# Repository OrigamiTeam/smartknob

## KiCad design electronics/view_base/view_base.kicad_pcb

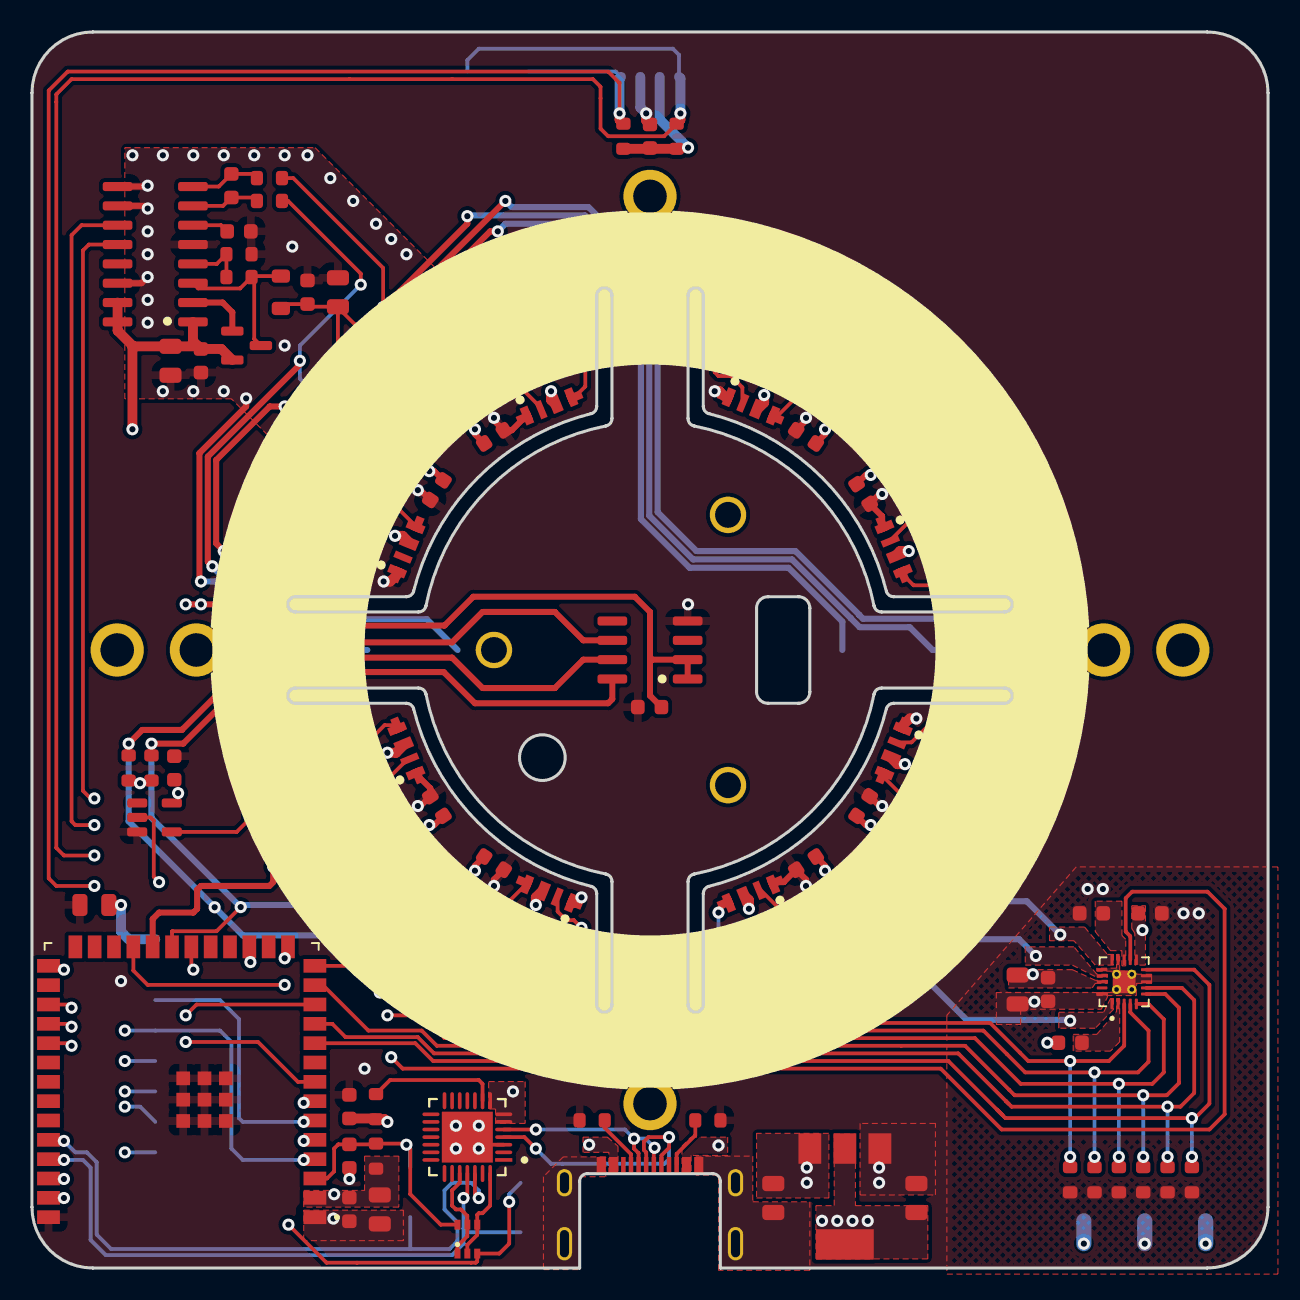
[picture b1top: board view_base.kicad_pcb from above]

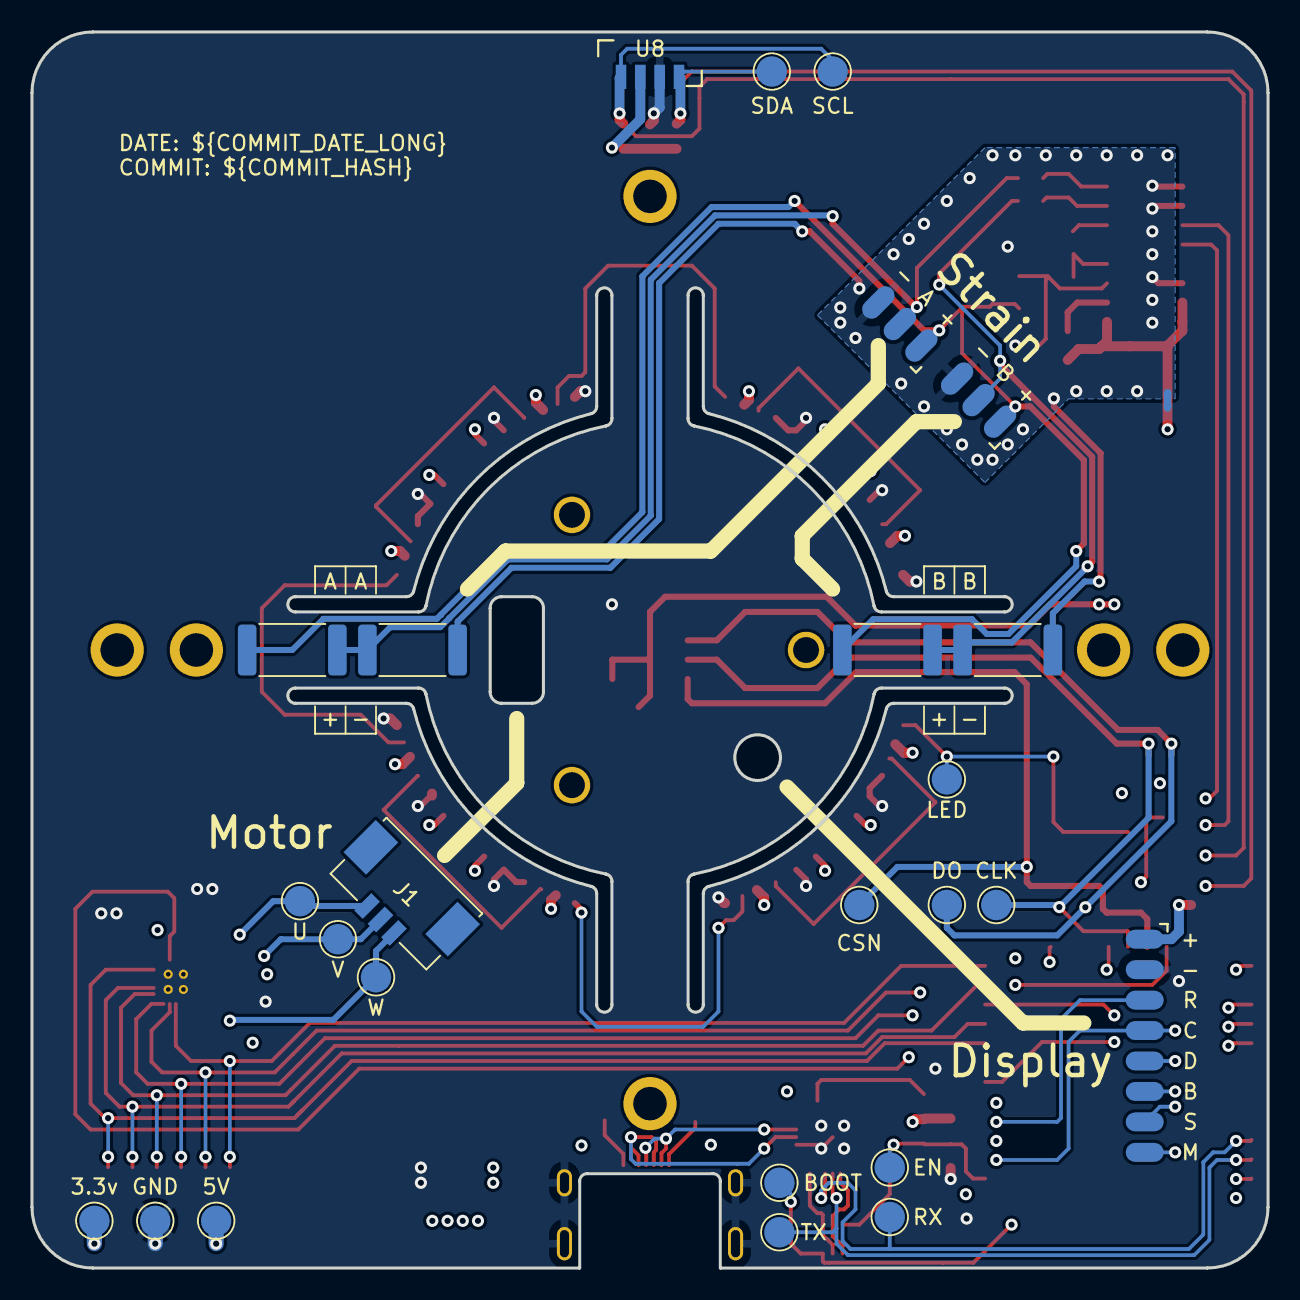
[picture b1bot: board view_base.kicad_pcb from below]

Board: 4 copper layers, 81.2 x 81.2 mm, 107 parts (26 on the bottom side), 58 nets.

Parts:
C1, C2, C3, C4, C5, C6, C7, C8, C11, C12, C14, C15, C17, C19, C20, C21, C22, C23, C25, C27, C29: 0.1uF; C_0603_1608Metric
C9, C10, C16, C18, C24, C26: 10uF; C_0805_2012Metric
C13: 22uF; C_0805_2012Metric
C28: 1uF; C_0603_1608Metric
D1, D2, D3, D4, D5, D6, D7, D8: SK6812SIDE-A; SK6812-SIDE-A
H1, H2, H3: MotorHole; MountingHole_M1.6
H4, H5, H6, H7: MountHole; MountingHole_2.2mm_M2_ISO7380_Pad_NonVirtual
H8, H9: AlignmentHole; MountingHole_2.2mm_M2_ISO7380_Pad_NonVirtual
J1: BLDC; 532610371
J2: USB_C_Receptacle_USB2.0; USB4510_NoPaste
J3: LCD; SolderPads_2mm_8
J4: A; SolderPads_2mm_3_STRAIN
J5: B; SolderPads_2mm_3_STRAIN
L1: 3.3uH; L_0805_2012Metric
NT1: NetTie_2; NetTie-2_SMD_Pad0.5mm
Q1: MMBT4403; SOT-23
Q2: UMH3N; SOT-363_SC-70-6
R1, R2: 5.1k; R_0603_1608Metric
R3, R7, R8, R9, R10, R11, R12, R17: 10k; R_0603_1608Metric
R4: 8.2k; R_0603_1608Metric
R5, R6: 100; R_0603_1608Metric
R13, R14, R15, R16: 2.2k; R_0603_1608Metric
R18, R19, R20, R21: 330; R_2512_6332Metric
R22: 1K; R_0603_1608Metric
TP1: 5V; TestPoint_Pad_D2.0mm_ValueSilk
TP2: 3.3v; TestPoint_Pad_D2.0mm_ValueSilk
TP3: GND; TestPoint_Pad_D2.0mm_ValueSilk
TP4: SDA; TestPoint_Pad_D2.0mm_ValueSilk
TP5: SCL; TestPoint_Pad_D2.0mm_ValueSilk
TP6: U; TestPoint_Pad_D2.0mm_ValueSilk
TP7: V; TestPoint_Pad_D2.0mm_ValueSilk
TP8: W; TestPoint_Pad_D2.0mm_ValueSilk
TP9: CSN; TestPoint_Pad_D2.0mm_ValueSilk
TP10: CLK; TestPoint_Pad_D2.0mm_ValueSilk
TP11: DO; TestPoint_Pad_D2.0mm_ValueSilk
TP12: LED; TestPoint_Pad_D2.0mm_ValueSilk
TP13: EN; TestPoint_Pad_D2.0mm_ValueSilk
TP14: BOOT; TestPoint_Pad_D2.0mm_ValueSilk
TP15: TX; TestPoint_Pad_D2.0mm_ValueSilk
TP16: RX; TestPoint_Pad_D2.0mm_ValueSilk
U1: MT6701-CT; SOIC-8_3.9x4.9mm_P1.27mm
U2: CP2102N-A02-GQFN28; Silicon_Labs-CP2102N-A02-GQFN28-IPC_A
U4: HX711; SOIC-16_3.9x9.9mm_P1.27mm
U5: TMC6300; QFN-20-1EP_3x3mm_P0.4mm_EP1.65x1.65mm_ThermalVias_LargerVia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
U7: SN74LV1T34DBV; SOT-23-5
U8: VEML7700; VEML7700-TOP
U9: TS1117BCW33_RPG; SOT-223-3_TabPin2_GndOutIn
U10: ESP32-S3-WROOM-1-N8R8; XCVR_ESP32S3WROOM1N8R8U
Z5: dummy_keepouts; ViewKeepouts3d
Z6, Z7, Z8: RotorScrew (BOM-only); bom_only_no_pin
Z9: WatchGlass39.5mm; bom_only_no_pin
Z10: BLDCMotor; bom_only_no_pin

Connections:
+3V3: C10.1, C11.1, C12.1, C16.1, C17.1, C20.1, C24.1, C25.1, C26.1, C27.1, J3.1, Q1.2 (E), R13.1, R14.1, R15.1, R16.2, R17.1, R22.1, TP2.1, U1.1 (VDD), U1.2 (MODE), U2.6 (VDD), U2.7 (VREGIN), U2.8 (VBUS), U4.1 (VSUP), U4.15 (RATE), U4.16 (DVDD), U5.11 (VIO/~STDBY), U8.2 (VDD), U9.2 (Output), U10.2 (3V3)
+5V: C1.1, C2.1, C3.1, C4.1, C5.1, C6.1, C7.1, C8.1, C9.1, C13.1, C14.1, C15.1, C29.1, D1.2 (VDD), D2.2 (VDD), D3.2 (VDD), D4.2 (VDD), D5.2 (VDD), D6.2 (VDD), D7.2 (VDD), D8.2 (VDD), J2.A4 (VBUS), J2.A9 (VBUS), J2.B4 (VBUS), J2.B9 (VBUS), TP1.1, U5.18 (VS), U7.5 (VCC), U9.3 (Input)
/DTR: Q2.2 (B1), Q2.4 (E2), U2.28 (DTR)
/ESP32_BOOT: Q2.3 (C2), TP14.1, U10.27 (IO0)
/ESP32_EN: C28.1, Q2.6 (C1), R17.2, TP13.1, U10.3 (EN)
/LCD_BACKLIGHT: J3.6, U10.5 (IO5)
/LCD_CMD: J3.8, U10.38 (IO2)
/LCD_CS: J3.7, U10.17 (IO9)
/LCD_DATA: J3.5, U10.15 (IO3)
/LCD_RST: J3.3, U10.6 (IO6)
/LCD_SCK: J3.4, U10.4 (IO4)
/LED_DATA_3V3: U7.2 (A), U10.7 (IO7)
/LED_DATA_5V: D1.1 (DIN), TP12.1, U7.4 (Y)
/MAG_CLK: R16.1, TP10.1, U1.7 (B/V/SCL/CLK), U10.21 (IO13)
/MAG_CSN: TP9.1, U1.8 (Z/W/CSN), U10.22 (IO14)
/MAG_DO: R15.2, TP11.1, U1.6 (A/U/SDA/DO), U10.30 (IO37)
/RTS: Q2.1 (E1), Q2.5 (B2), U2.24 (RTS)
/SCL: R14.2, TP5.1, U8.1 (SCL), U10.12 (IO8)
/SDA: R13.2, TP4.1, U8.4 (SDA), U10.8 (IO15)
/STRAIN_DO: U4.12 (DOUT), U10.31 (IO38)
/STRAIN_E+: C18.1, C19.1, J4.1, J5.1, L1.2, R18.1, R20.2
/STRAIN_S+: J4.2, R6.1, R18.2, R19.1
/STRAIN_S-: J5.2, R5.2, R20.1, R21.2
/STRAIN_SCK: U4.11 (PD_SCK), U10.39 (IO1)
/TMC_DIAG: U5.12 (DIAG), U10.29 (IO36)
/TMC_UH: R7.1, U5.3 (UH), U10.14 (IO20)
/TMC_UL: R10.1, U5.6 (UL), U10.13 (IO19)
/TMC_VH: R8.1, U5.4 (VH), U10.23 (IO21)
/TMC_VL: R12.1, U5.10 (VL), U10.10 (IO17)
/TMC_WH: R9.1, U5.5 (WH), U10.20 (IO12)
/TMC_WL: R11.1, U5.7 (WL), U10.11 (IO18)
/USB_CC1: J2.A5 (CC1), R1.1
/USB_CC2: J2.B5 (CC2), R2.1
/USB_D+: J2.A6 (D+), J2.B6 (D+), U2.4 (D+)
/USB_D-: J2.A7 (D-), J2.B7 (D-), U2.5 (D-)
/USB_SERIAL_RXI: TP15.1, U2.25 (RXD), U10.37 (TXD0)
/USB_SERIAL_TXO: TP16.1, U2.26 (TXD), U10.36 (RXD0)
GND: C1.2, C2.2, C3.2, C4.2, C5.2, C6.2, C7.2, C8.2, C9.2, C10.2, C11.2, C13.2, C14.2, C17.2, C20.2, C21.2, C24.2, C25.2, C26.2, C27.2, C28.2, C29.2, D1.4 (VSS), D2.4 (VSS), D3.4 (VSS), D4.4 (VSS), D5.4 (VSS), D6.4 (VSS), D7.4 (VSS), D8.4 (VSS), J2.A1 (GND), J2.A12 (GND), J2.B1 (GND), J2.B12 (GND), J2.S1 (SHIELD), J3.2, NT1.2, R1.2, R2.2, R7.2, R8.2, R9.2, R10.2, R11.2, R12.2, TP3.1, U1.4 (GND), U2.3 (GND), U2.29 (GND), U5.8 (GND), U5.9 (GND), U5.14 (GND), U5.16 (BRUV), U5.20 (BRW), U5.PAD, U7.3 (GND), U8.3 (GND), U9.1 (GND), U10.1 (GND), U10.40 (GND), U10.41_1 (GND), U10.41_2 (GND), U10.41_3 (GND), U10.41_4 (GND), U10.41_5 (GND), U10.41_6 (GND), U10.41_7 (GND), U10.41_8 (GND), U10.41_9 (GND)
GNDA: C12.2, C16.2, C18.2, C19.2, C22.1, J4.3, J5.3, NT1.1, R4.2, R19.2, R21.1, U4.5 (AGND), U4.9 (INB-), U4.10 (INB+), U4.14 (XI)
unnamed: D1.3 (DOUT), D2.1 (DIN)
unnamed: D2.3 (DOUT), D3.1 (DIN)
unnamed: D3.3 (DOUT), D4.1 (DIN)
unnamed: D4.3 (DOUT), D5.1 (DIN)
unnamed: D5.3 (DOUT), D6.1 (DIN)
unnamed: D6.3 (DOUT), D7.1 (DIN)
unnamed: D7.3 (DOUT), D8.1 (DIN)
unnamed: J1.1, TP8.1, U5.1 (W)
unnamed: J1.2, TP7.1, U5.17 (V)
unnamed: J1.3, TP6.1, U5.15 (U)
unnamed: Q1.1 (B), U4.2 (BASE)
unnamed: L1.1, Q1.3 (C), R3.1, U4.3 (AVDD)
unnamed: R22.2, U2.9 (~RST)
unnamed: C23.1, R6.2, U4.8 (INA+)
unnamed: C23.2, R5.1, U4.7 (INA-)
unnamed: C22.2, U4.6 (VBG)
unnamed: R3.2, R4.1, U4.4 (VFB)
unnamed: C21.1, U5.13 (1V8OUT)
unnamed: C15.2, U5.2 (VCP)

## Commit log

2023-10-07 Updated to esp32s3, cp2102, re-routed
2023-10-18 refactored PCB
2023-10-20 working screen, motor, magnet sensor
2023-10-22 fixed strain sensor

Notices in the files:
parts and their libraries:
Copyright 2021 Accelerated Designs. All rights reserved.
